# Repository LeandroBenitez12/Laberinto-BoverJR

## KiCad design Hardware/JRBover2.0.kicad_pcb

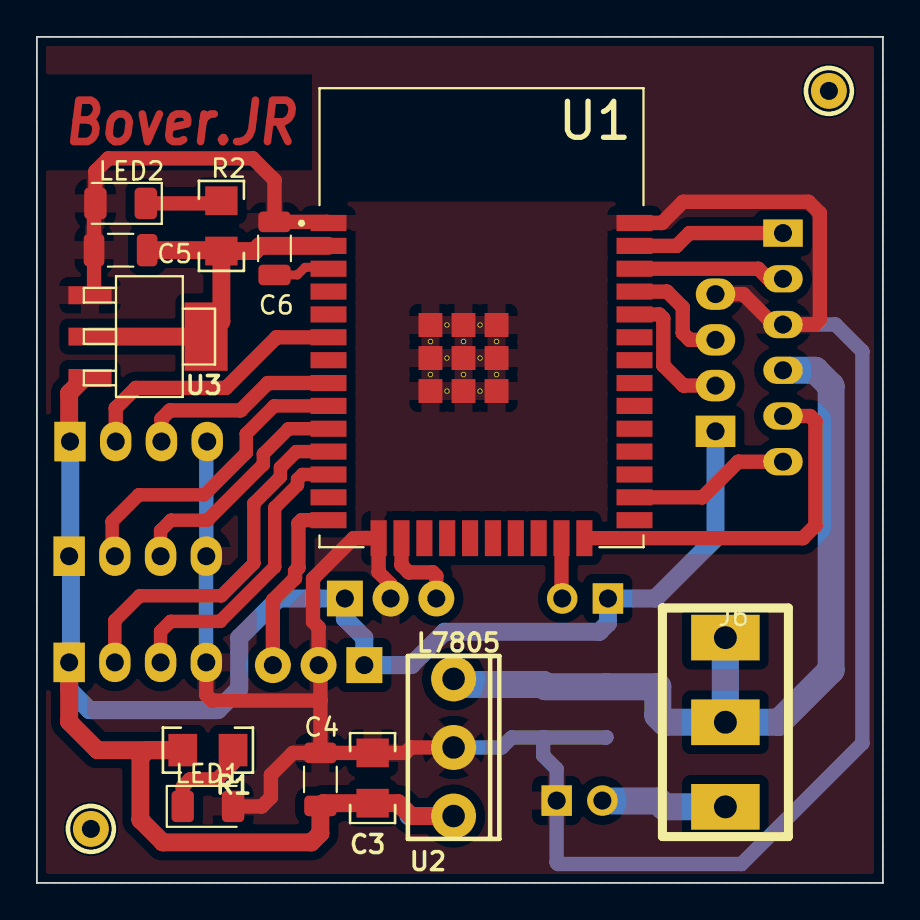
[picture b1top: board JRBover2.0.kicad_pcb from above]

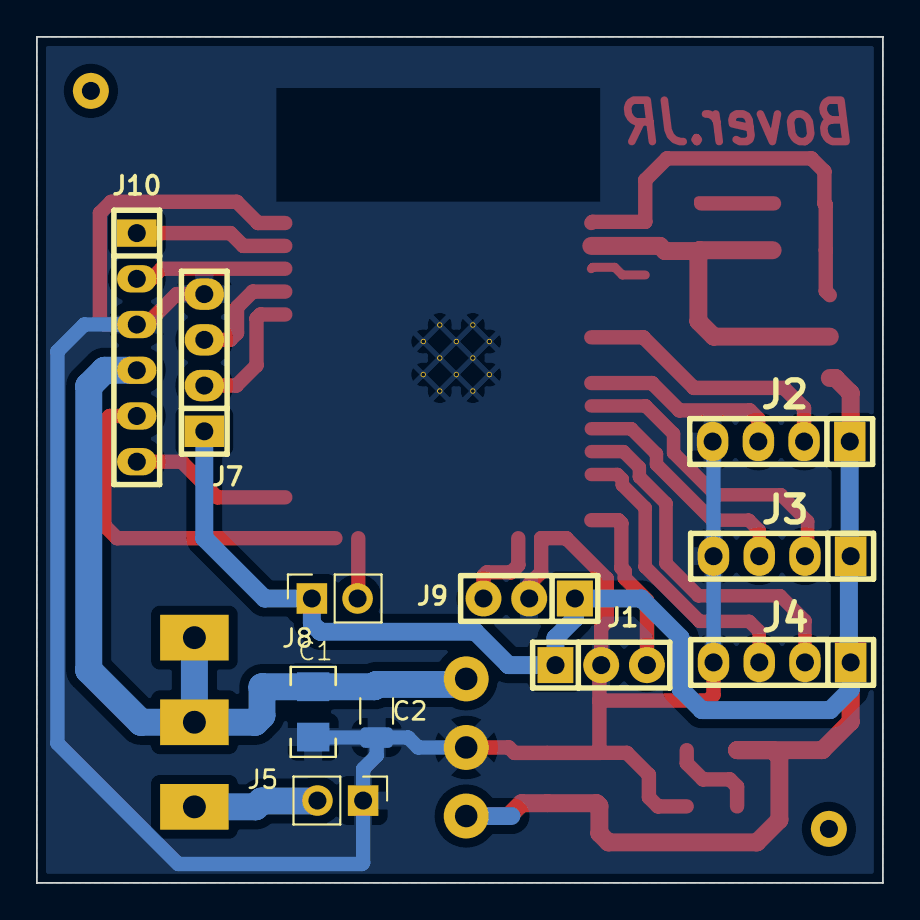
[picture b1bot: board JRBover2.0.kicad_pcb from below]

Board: 2 copper layers, 47.0 x 47.0 mm, 25 parts (11 on the bottom side), 23 nets.

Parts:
C1: 220uF; C_1206
C2, C4, C5: 100nF; C_1206_3216Metric
C3: 10uF; C_1206
C6: 1uF; C_1206_3216Metric
H1, H2: Mounting_Hole; pad_2mm
J1: EncoderMotorDerecha; Pin_Strip_3
J2, J3, J4: HC_SRO4; pin_strip_4
J5: CableAlimentacion; PinHeader_1x02_P2.54mm_Vertical
J6: SWITCH; SW_SPDT_TH_Vertical
J7: Programador; pin_strip_4
J8: BOTON; PinSocket_1x02_P2.54mm_Vertical
J9: EncoderMotorIzquierda; Pin_Strip_3
J10: Input of Driver L9110; Pin_Header_6
LED1, LED2: 2V; LED_1206_3216Metric
R1: 470; R_1206
R2: 330; R_1206
U1: ESP32-WROOM-32; Chipesp32
U2: L7805; to220
U3: LM1117-SOT; SOT223

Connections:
+3V3: C5.2, R2.2, U1.2 (3V3), U3.2 (VOUT), U3.4 (VOUT)
+5V: C3.1, C4.2, J1.1, J2.1, J3.1, J4.1, J7.1, J8.1, J9.1, R1.2, U2.3 (OUT), U3.3 (VIN)
+7.5V: C1.1, C2.1, J6.2, J6.3, J10.4, U2.1 (IN)
/BOTON: J8.2, U1.23 (IO15)
/D0: J1.3, U1.14 (IO12)
/D0B: J9.3, U1.16 (IO13)
/Echo: J2.2, U1.6 (IO34)
/Echo2: J3.2, U1.9 (IO33)
/Echo3: J4.2, U1.11 (IO26)
/IN1: J10.6, U1.26 (IO4)
/IN2: J10.5, U1.24 (IO2)
/IN3: J10.2, U1.36 (IO22)
/IN4: J10.1, U1.37 (IO23)
/RX: J7.2, U1.34 (RXD0)
/TX: J7.3, U1.35 (TXD0)
/Trig1: J2.3, U1.8 (IO32)
/Trig2: J3.3, U1.10 (IO25)
/Trig3: J4.3, U1.12 (IO27)
/VBAT: J5.2, J6.1
GND: C1.2, C2.2, C3.2, C4.1, C5.1, C6.2, J1.2, J2.4, J3.4, J4.4, J5.1, J7.4, J9.2, J10.3, LED1.2 (K), LED2.2 (K), U1.1 (GND), U1.15 (GND), U1.38 (GND), U1.39_1 (GND), U1.39_2 (GND), U1.39_3 (GND), U1.39_4 (GND), U1.39_5 (GND), U1.39_6 (GND), U1.39_7 (GND), U1.39_8 (GND), U1.39_9 (GND), U1.39_10 (GND), U1.39_11 (GND), U1.39_12 (GND), U1.39_13 (GND), U1.39_14 (GND), U1.39_15 (GND), U1.39_16 (GND), U1.39_17 (GND), U1.39_18 (GND), U1.39_19 (GND), U1.39_20 (GND), U1.39_21 (GND), U2.2 (GND), U3.1 (ADJ/GND)
unnamed: C6.1, U1.3 (EN)
unnamed: LED1.1 (A), R1.1
unnamed: LED2.1 (A), R2.1

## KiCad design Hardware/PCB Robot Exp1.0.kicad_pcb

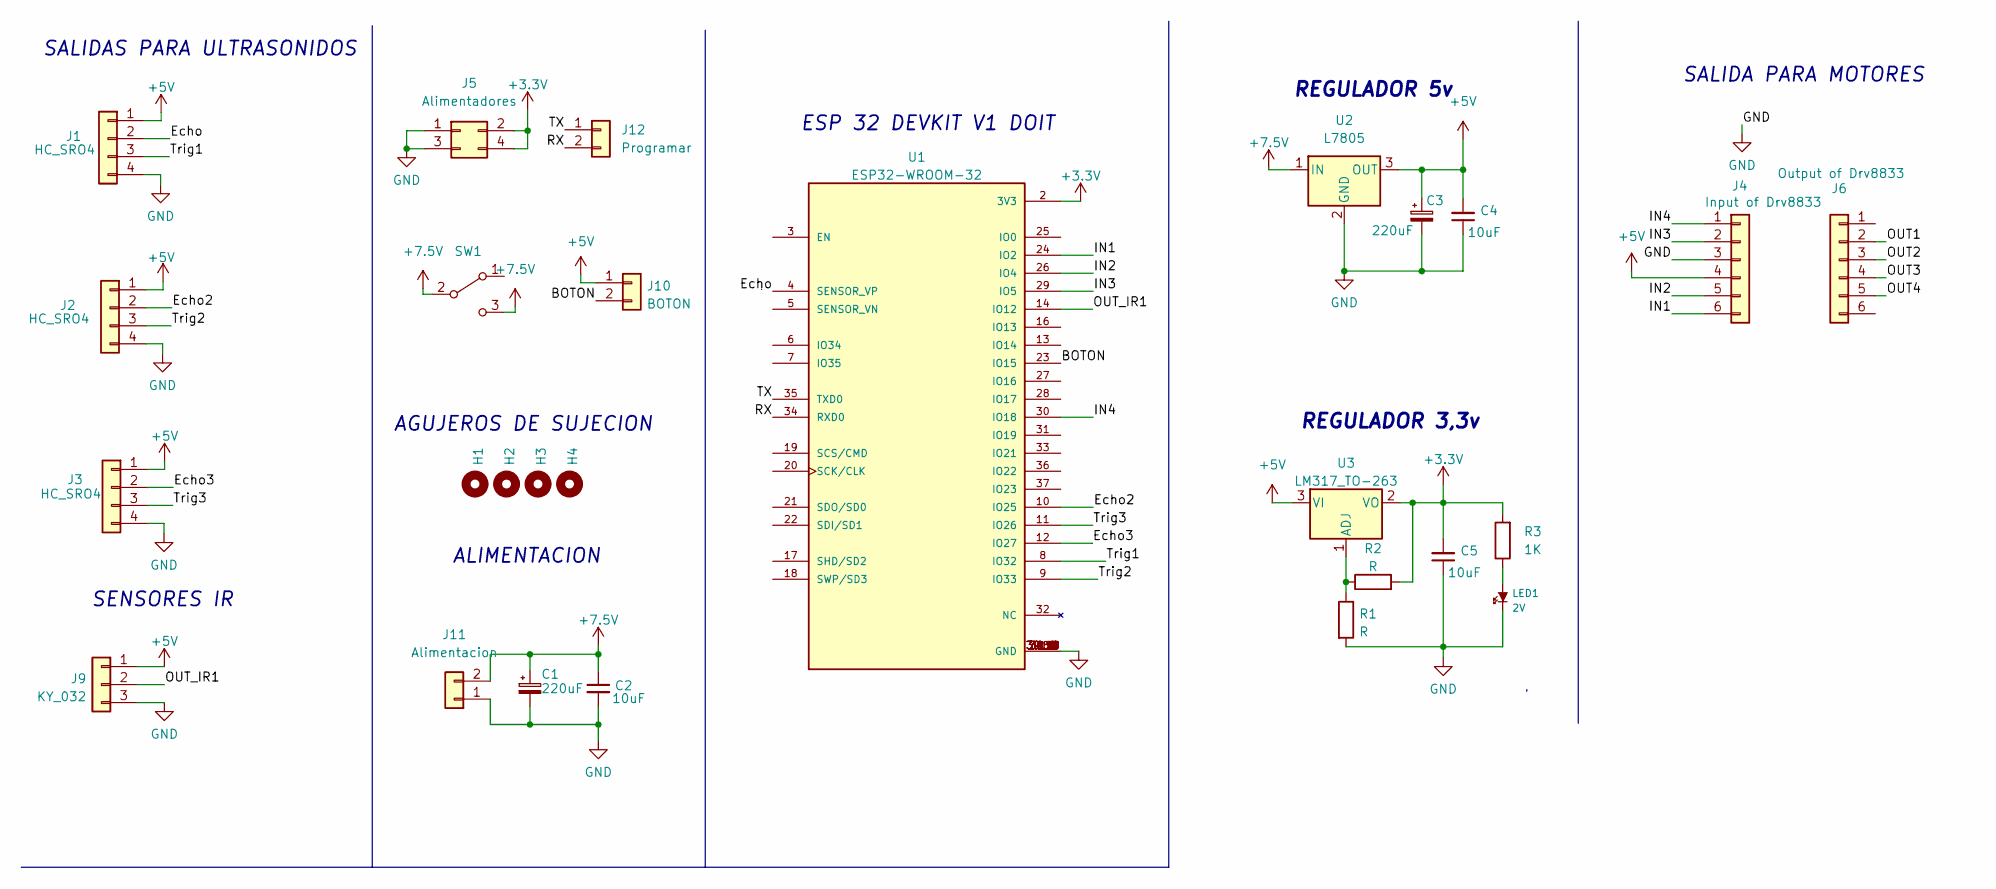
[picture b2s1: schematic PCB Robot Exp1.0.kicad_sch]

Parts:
C1, C3: 220uF; C_1206
C2, C4, C5: 10uF; C_0805_2012Metric_Pad1.18x1.45mm_HandSolder
H1, H2, H3, H4: Mounting_Hole; pad_2mm
J1, J2, J3: HC_SRO4; pin_strip_4
J4: Input of Drv8833; Pin_Header_6
J5: Alimentadores; PinHeader_2x02_P2.00mm_Vertical
J6: Output of Drv8833; Pin_Header_6
J9: KY_032; Pin_Strip_3
J10: BOTON; PinSocket_1x02_P2.54mm_Vertical
J11: Alimentacion; PinHeader_1x02_P2.54mm_Vertical
J12: Programar; PinHeader_1x02_P2.54mm_Vertical
LED1: 2V; Led_0805
R1, R2: R; R_1206
R3: 1K; R_0805
SW1: SW_SPDT; SW_SPDT_TH_Vertical
U1: ESP32-WROOM-32; MODULE_ESP32-WROOM-32; PARTREV 2.9
U2: L7805; to220
U3: LM317_TO-263; TO-263-2

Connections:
+3V3: C5.2, J5.2, J5.4, R2.2, R3.2, U1.2 (3V3), U3.2 (VO)
+5V: C3.1, C4.2, J1.1, J2.1, J3.1, J4.4, J9.1, J10.1, U2.3 (OUT), U3.3 (VI)
+7.5V: C1.1, C2.1, J11.2, SW1.2 (B), SW1.3 (C), U2.1 (IN)
/BOTON: J10.2, U1.23 (IO15)
/Echo: J1.2, U1.4 (SENSOR_VP)
/Echo2: J2.2, U1.10 (IO25)
/Echo3: J3.2, U1.12 (IO27)
/IN1: J4.6, U1.24 (IO2)
/IN2: J4.5, U1.26 (IO4)
/IN3: J4.2, U1.29 (IO5)
/IN4: J4.1, U1.30 (IO18)
/OUT1: J6.2
/OUT2: J6.3
/OUT3: J6.4
/OUT4: J6.5
/OUT_IR1: J9.2, U1.14 (IO12)
/RX: J12.2, U1.34 (RXD0)
/TX: J12.1, U1.35 (TXD0)
/Trig1: J1.3, U1.8 (IO32)
/Trig2: J2.3, U1.9 (IO33)
/Trig3: J3.3, U1.11 (IO26)
GND: C1.2, C2.2, C3.2, C4.1, C5.1, J1.4, J2.4, J3.4, J4.3, J5.1, J5.3, J9.3, J11.1, LED1.2 (K), R1.2, U1.1 (GND), U1.15 (GND), U1.38 (GND), U1.39_1 (GND), U1.39_2 (GND), U1.39_3 (GND), U1.39_4 (GND), U1.39_5 (GND), U1.39_6 (GND), U1.39_7 (GND), U1.39_8 (GND), U1.39_9 (GND), U1.39_10 (GND), U1.39_11 (GND), U1.39_12 (GND), U1.39_13 (GND), U1.39_14 (GND), U1.39_15 (GND), U1.39_16 (GND), U1.39_17 (GND), U1.39_18 (GND), U1.39_19 (GND), U1.39_20 (GND), U1.39_21 (GND), U2.2 (GND)
unnamed: LED1.1 (A), R3.1
unnamed: R1.1, R2.1, U3.1 (ADJ)

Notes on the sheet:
ALIMENTACION
AGUJEROS DE SUJECION
SENSORES IR
ESP 32 DEVKIT V1 DOIT
REGULADOR 3,3v
SALIDAS PARA ULTRASONIDOS
REGULADOR 5v
SALIDA PARA MOTORES

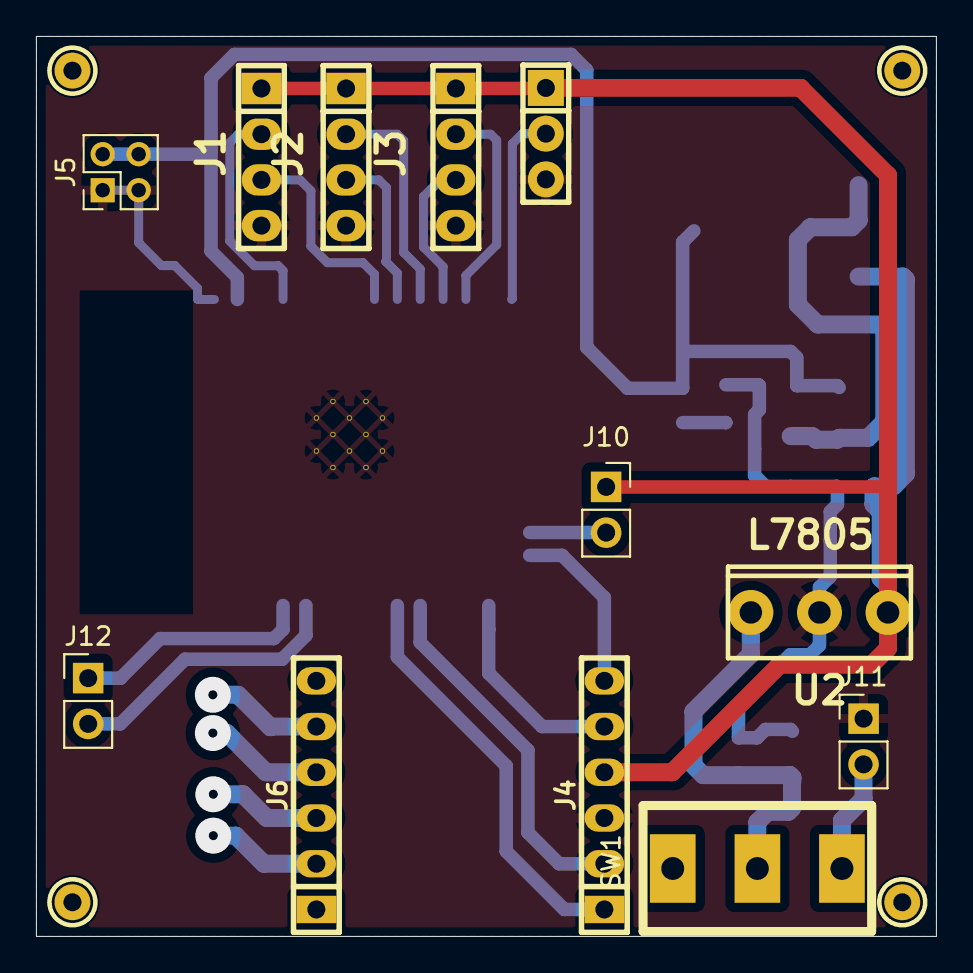
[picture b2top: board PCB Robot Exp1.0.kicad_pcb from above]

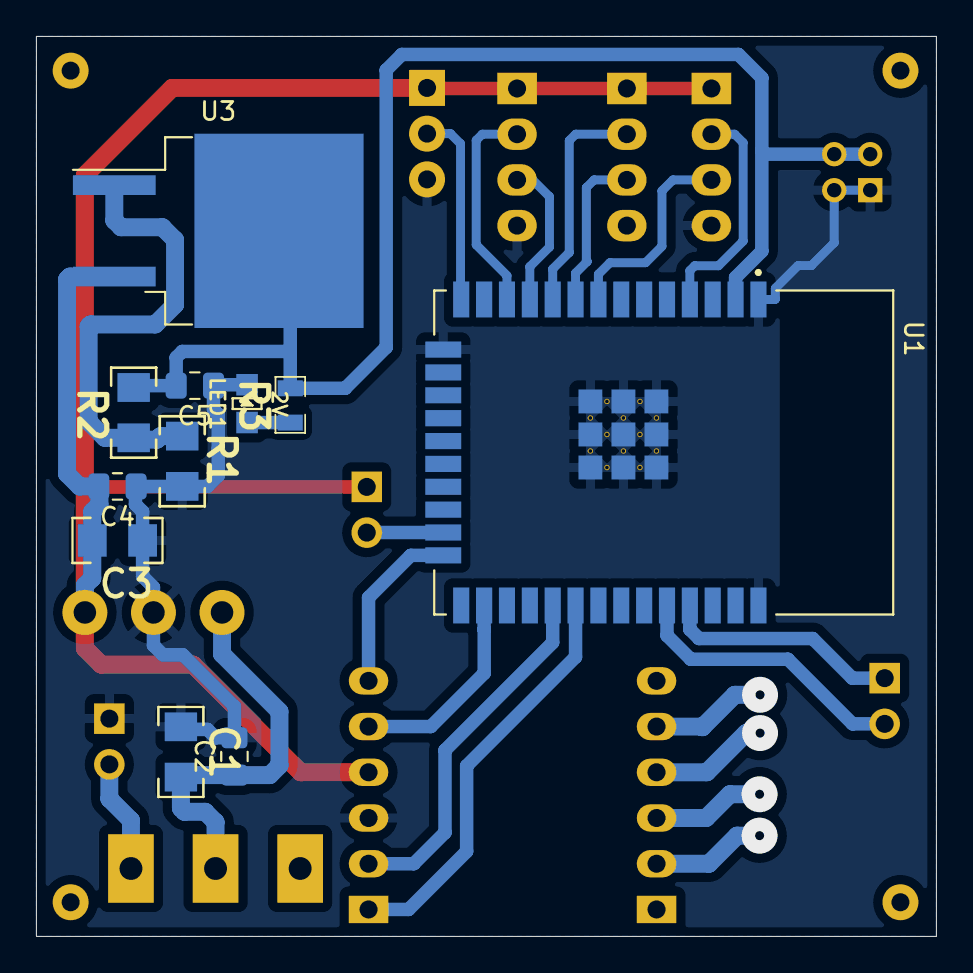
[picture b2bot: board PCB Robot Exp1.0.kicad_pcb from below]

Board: 2 copper layers, 50.0 x 50.0 mm, 27 parts (11 on the bottom side), 20 nets.

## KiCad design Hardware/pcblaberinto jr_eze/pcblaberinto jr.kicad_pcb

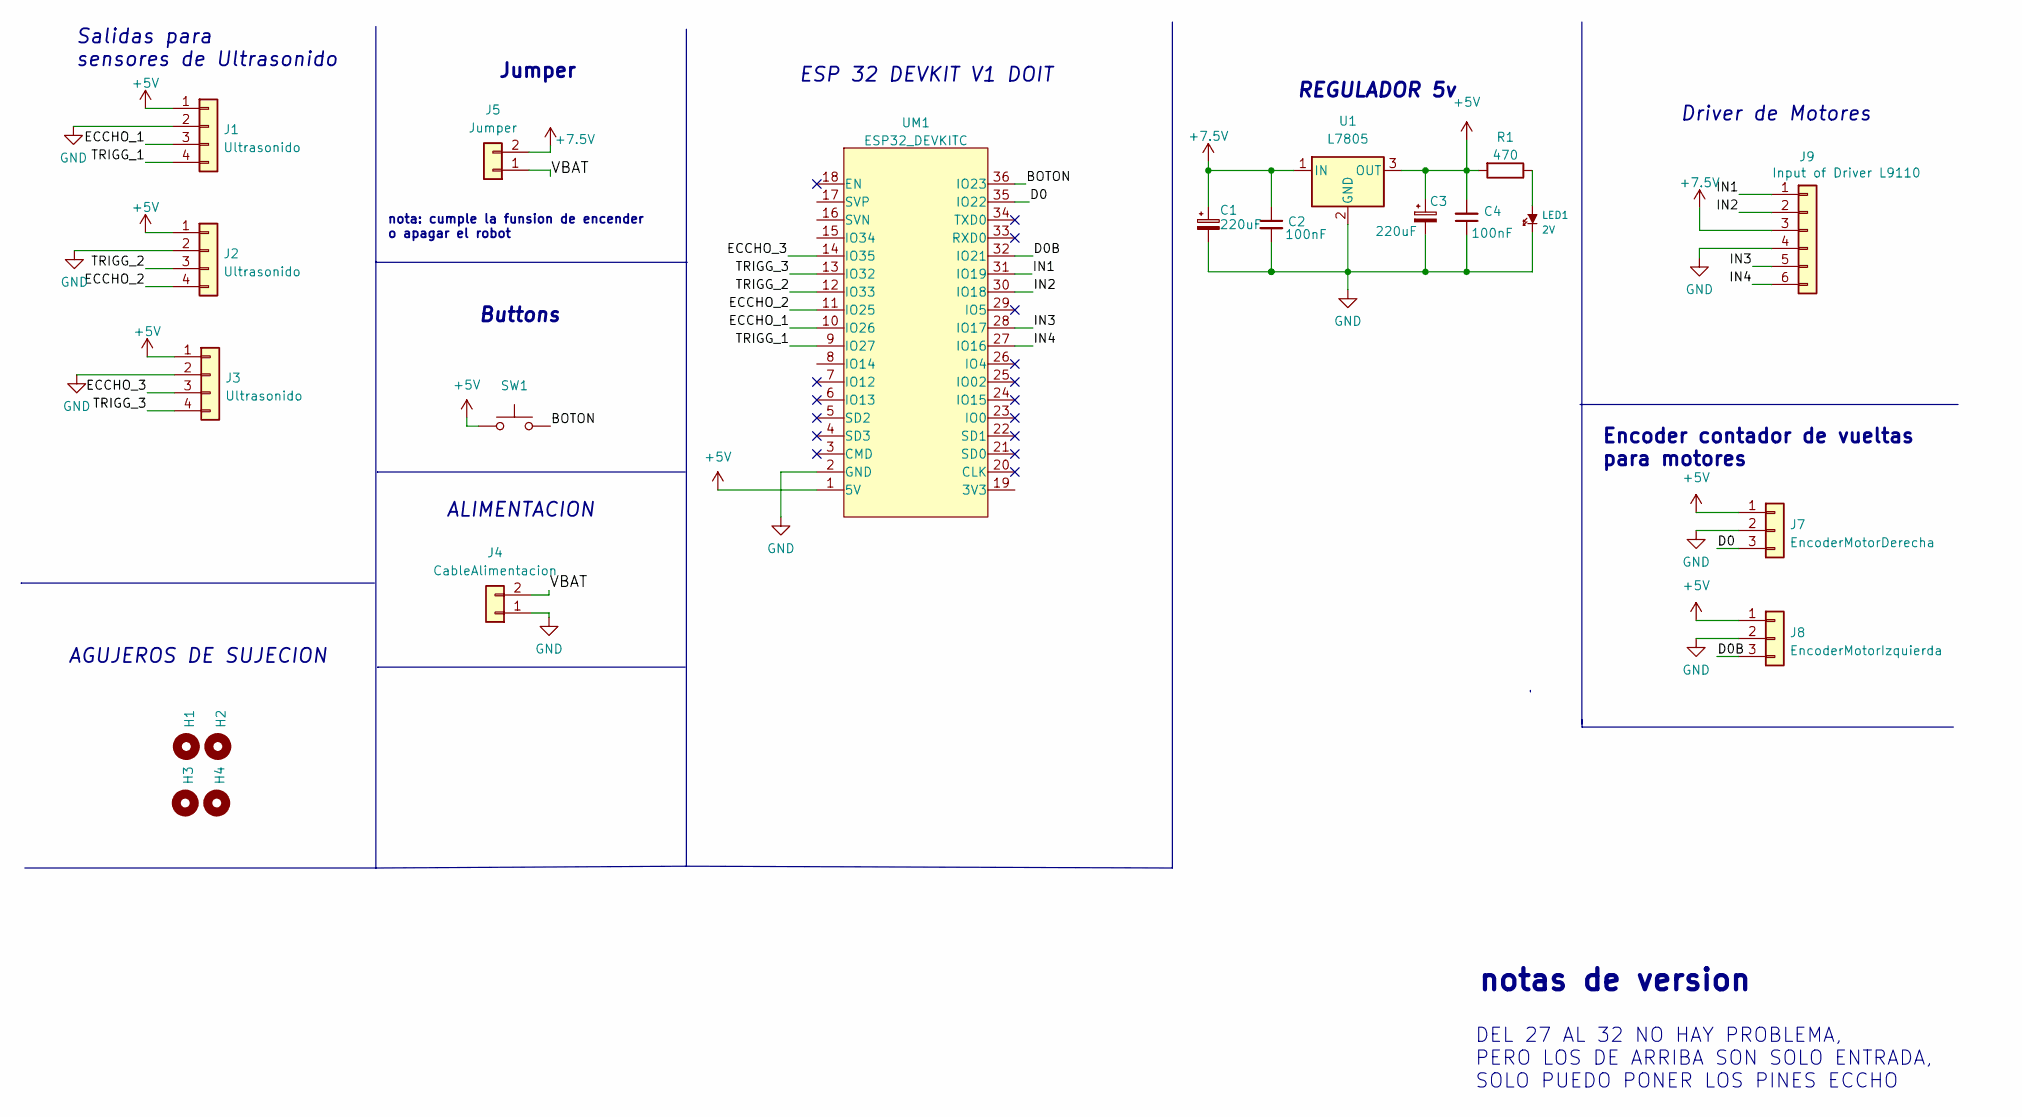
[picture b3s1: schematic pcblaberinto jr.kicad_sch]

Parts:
C1, C3: 220uF; CAP_ELEC_5x11mm
C2, C4: 100nF; C_1206_3216Metric
H1, H2, H3, H4: Mounting_Hole; hole_3mm
J1, J2, J3: Ultrasonido; JST_EH_B4B-EH-A_1x04_P2.50mm_Vertical
J4: CableAlimentacion; JST_EH_B2B-EH-A_1x02_P2.50mm_Vertical
J5: Jumper
J7: EncoderMotorDerecha; JST_EH_B3B-EH-A_1x03_P2.50mm_Vertical
J8: EncoderMotorIzquierda; JST_EH_B3B-EH-A_1x03_P2.50mm_Vertical
J9: Input of Driver L9110; JST_EH_B6B-EH-A_1x06_P2.50mm_Vertical
LED1: 2V; led_3mm_red
R1: 470; R_1206
SW1: SW_Push; SW_PUSH_6mm_H4.3mm
U1: L7805; to220
UM1: ESP32_DEVKITC

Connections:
+5V: C3.1, C4.2, J1.1, J2.1, J3.1, J7.1, J8.1, R1.2, SW1.1, U1.3 (OUT), UM1.1 (5V)
+7.5V: C1.1, C2.1, J5.2, J9.3, U1.1 (IN)
/BOTON: SW1.2, UM1.36 (IO23)
/D0: J7.3, UM1.35 (IO22)
/D0B: J8.3, UM1.32 (IO21)
/ECCHO_1: J1.3, UM1.10 (IO26)
/ECCHO_2: J2.4, UM1.11 (IO25)
/ECCHO_3: J3.3, UM1.14 (IO35)
/IN1: J9.1, UM1.31 (IO19)
/IN2: J9.2, UM1.30 (IO18)
/IN3: J9.5, UM1.28 (IO17)
/IN4: J9.6, UM1.27 (IO16)
/TRIGG_1: J1.4, UM1.9 (IO27)
/TRIGG_2: J2.3, UM1.12 (IO33)
/TRIGG_3: J3.4, UM1.13 (IO32)
/VBAT: J4.2, J5.1
GND: C1.2, C2.2, C3.2, C4.1, J1.2, J2.2, J3.2, J4.1, J7.2, J8.2, J9.4, LED1.2 (K), U1.2 (GND), UM1.2 (GND)
unnamed: LED1.1 (A), R1.1

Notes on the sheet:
nota: cumple la funsion de encender o apagar el robot
Buttons
Encoder contador de vueltas para motores
Jumper
AGUJEROS DE SUJECION
Driver de Motores
notas de version
ALIMENTACION
Salidas para sensores de Ultrasonido
DEL 27 AL 32 NO HAY PROBLEMA, PERO LOS DE ARRIBA SON SOLO ENTRADA, SOLO PUEDO PONER LOS PINES ECCHO
REGULADOR 5v
ESP 32 DEVKIT V1 DOIT

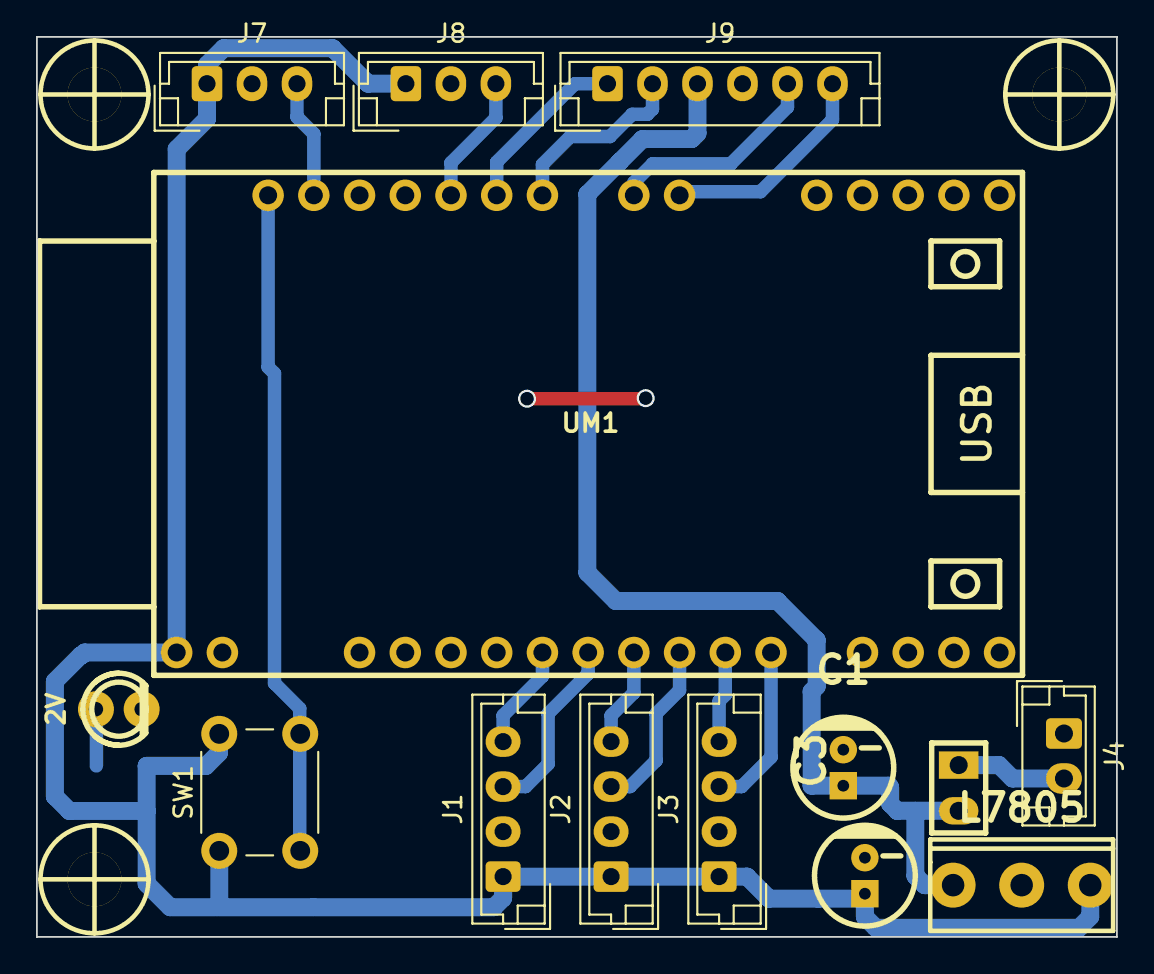
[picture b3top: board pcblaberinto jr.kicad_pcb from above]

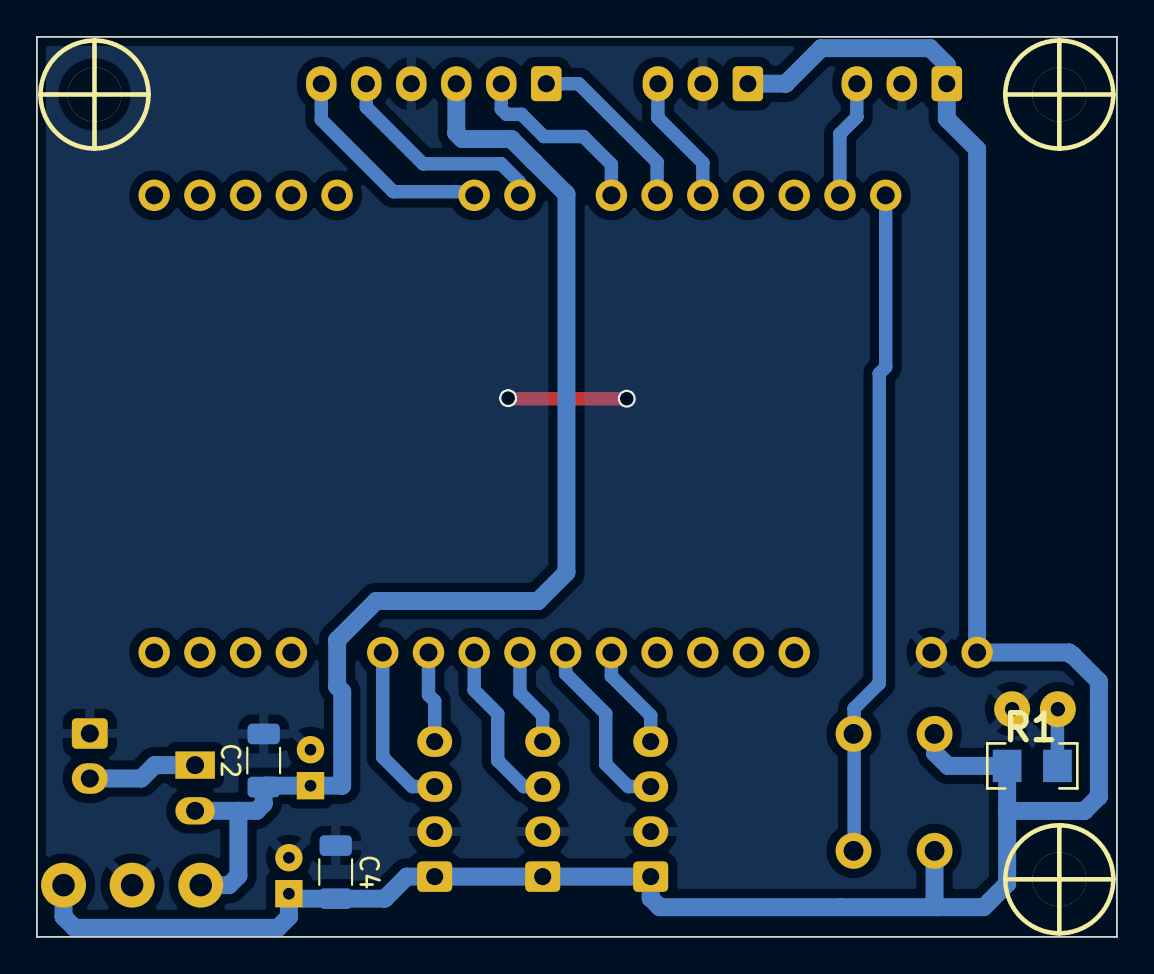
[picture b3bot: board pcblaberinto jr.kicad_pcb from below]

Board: 2 copper layers, 60.0 x 50.0 mm, 20 parts (3 on the bottom side), 18 nets.
